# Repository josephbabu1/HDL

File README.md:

THE CODES IN THIS FILES ARE STRICTLY EXPERIMENTAL

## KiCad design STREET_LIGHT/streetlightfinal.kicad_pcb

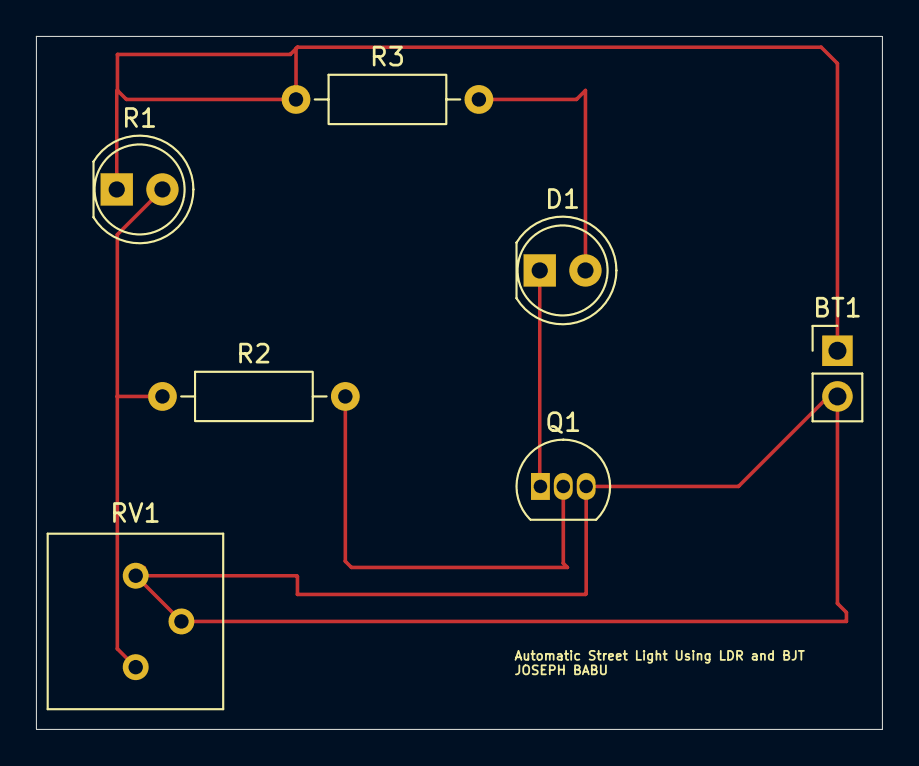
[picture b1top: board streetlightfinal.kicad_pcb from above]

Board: 2 copper layers, 47.0 x 38.5 mm, 7 parts (0 on the bottom side), 6 nets.

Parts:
BT1: 6V; PinHeader_1x02_P2.54mm_Vertical
D1: LED; LED_D5.0mm
Q1: BC547; TO-92_Inline
R1: LDR03; LED_D5.0mm
R2: 4.7K; R_Axial_DIN0207_L6.3mm_D2.5mm_P10.16mm_Horizontal
R3: 470; R_Axial_DIN0207_L6.3mm_D2.5mm_P10.16mm_Horizontal
RV1: 10K; Potentiometer_Bourns_3386P_Vertical

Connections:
unnamed: BT1.1 (+), R1.1, R3.1
unnamed: BT1.2 (-), Q1.3 (E), RV1.2, RV1.3
unnamed: D1.2 (A), R3.2
unnamed: D1.1 (K), Q1.1 (C)
unnamed: Q1.2 (B), R2.2
unnamed: R1.2, R2.1, RV1.1

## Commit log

2026-03-24 Create DIGITAL_VOLTMETER
2026-03-24 Create PSEUDO_RANDOM_NUMBER_GENERATOR
2026-04-10 Create SCHEMATICS_&_DIAGRAMS
2026-04-10 digital voltmeter schematic diagram
2026-06-24 Create 1
